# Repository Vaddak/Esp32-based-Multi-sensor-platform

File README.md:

# Esp32-based-Multi-sensor-platform
PCB for general testing with twelve 3.5mm jacks with five pines for sensoring.
The ESP32-DEVKKITV1 has 38 pinouts.

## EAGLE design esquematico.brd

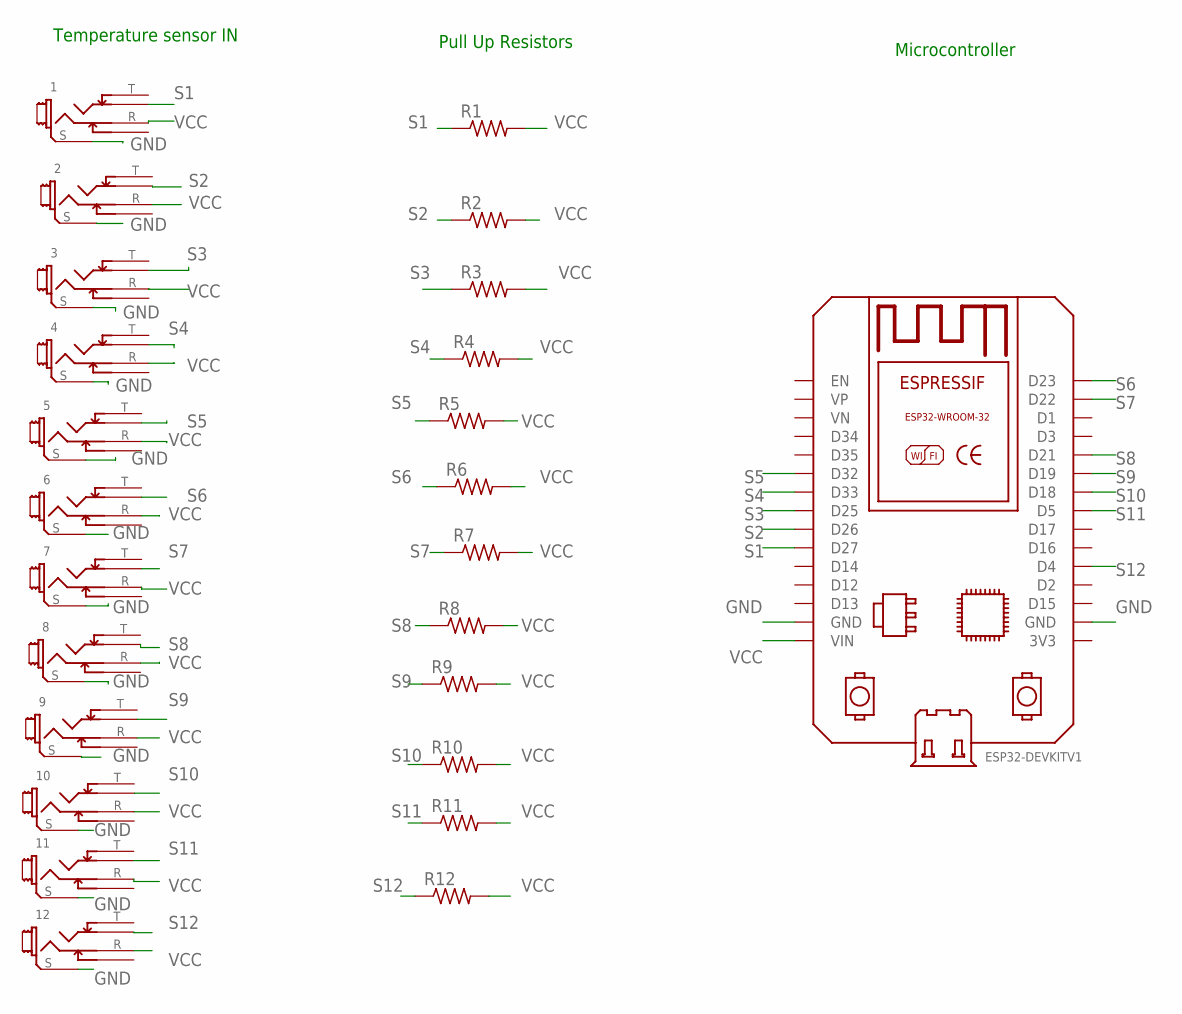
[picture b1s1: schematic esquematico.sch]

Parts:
1, 2, 3, 4, 5, 6, 7, 8, 9, 10, 11, 12: JACK-3.5MM; JACK-5PINES
BOARD1: ESP32DEVKITV1; ESP32-DEVKITV1
R1, R2, R3, R4, R5, R6, R7, R8, R9, R10, R11, R12: R-US_M0805; M0805

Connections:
GND: 1.S, 2.S, 3.S, 4.S, 5.S, 6.S, 7.S, 8.S, 9.S, 10.S, 11.S, 12.S, BOARD1.GND, BOARD1.GND@1 (GND)
S1: 1.T, BOARD1.D27, R1.1
S2: 2.T, BOARD1.D26, R2.1
S3: 3.T, BOARD1.D25, R3.1
S4: 4.T, BOARD1.D33, R4.1
S5: 5.T, BOARD1.D32, R5.1
S6: 6.T, BOARD1.D23, R6.1
S7: 7.T, BOARD1.D22, R7.1
S8: 8.T, BOARD1.D21, R8.1
S9: 9.T, BOARD1.D19, R9.1
S10: 10.T, BOARD1.D18, R10.1
S11: 11.T, BOARD1.D5, R11.1
S12: 12.T, BOARD1.D4, R12.1
VCC: 1.R, 2.R, 3.R, 4.R, 5.R, 6.R, 7.R, 8.R, 9.R, 10.R, 11.R, 12.R, BOARD1.VIN, R1.2, R2.2, R3.2, R4.2, R5.2, R6.2, R7.2, R8.2, R9.2, R10.2, R11.2, R12.2

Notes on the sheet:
Temperature sensor IN
Microcontroller
Pull Up Resistors

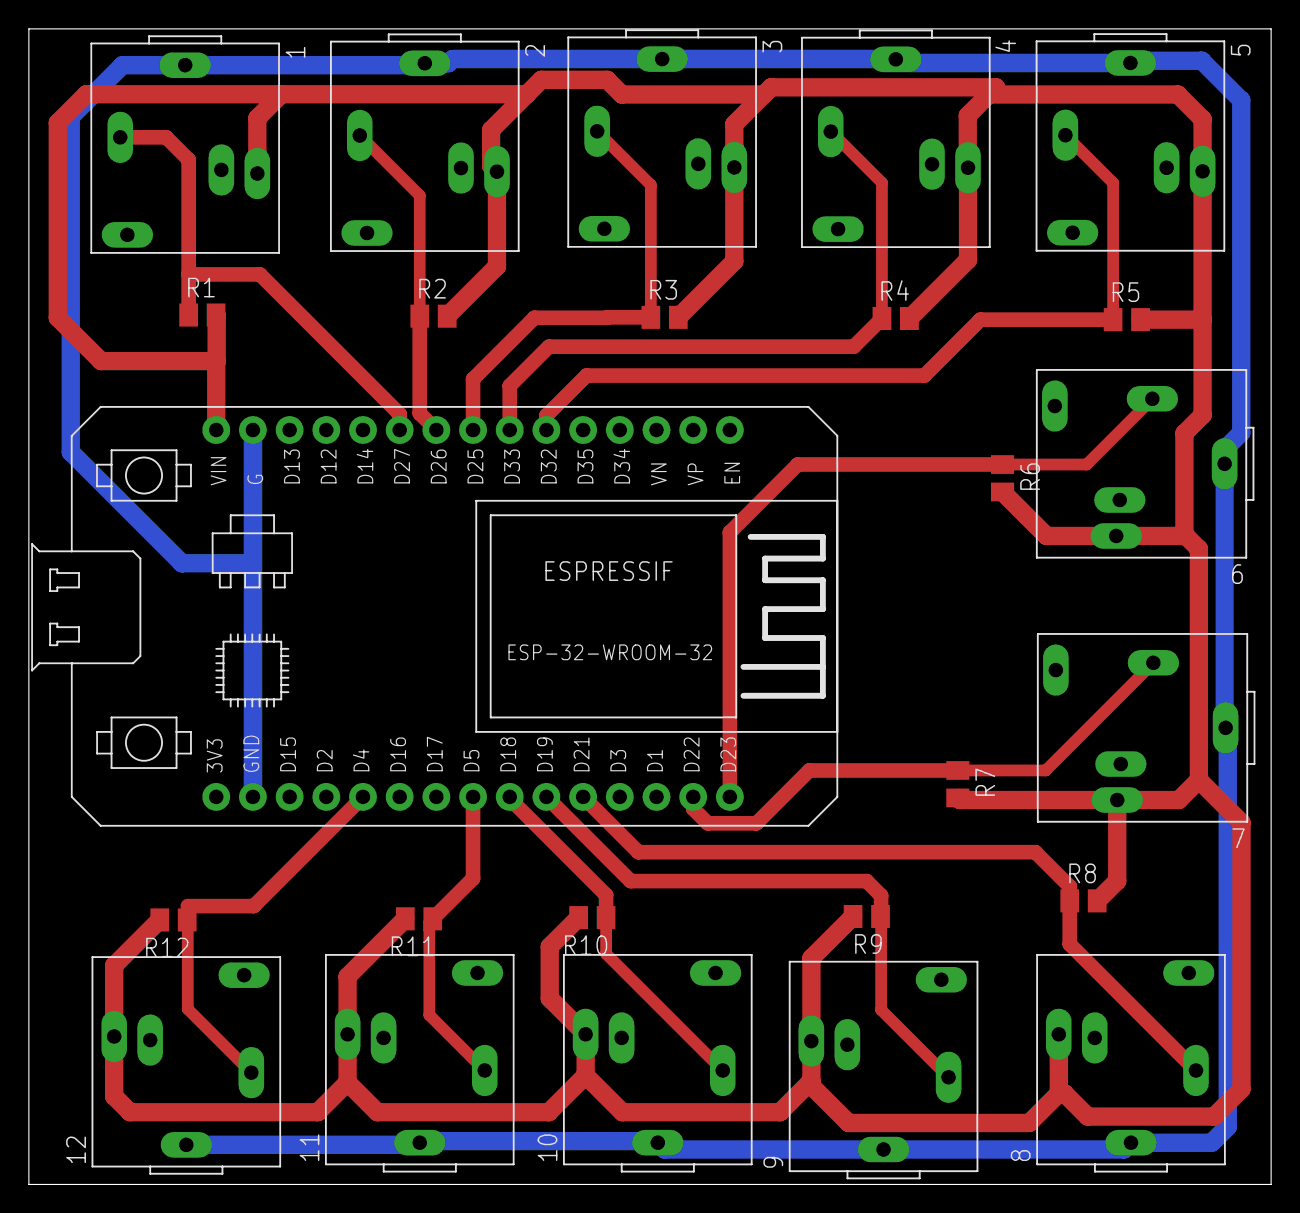
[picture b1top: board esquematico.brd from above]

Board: 2 copper layers, 86.0 x 80.0 mm, 25 parts (0 on the bottom side), 14 nets.
